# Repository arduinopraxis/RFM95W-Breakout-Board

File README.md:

# RFM95W-Breakout-Board
RFM92/95W Breakout-Board

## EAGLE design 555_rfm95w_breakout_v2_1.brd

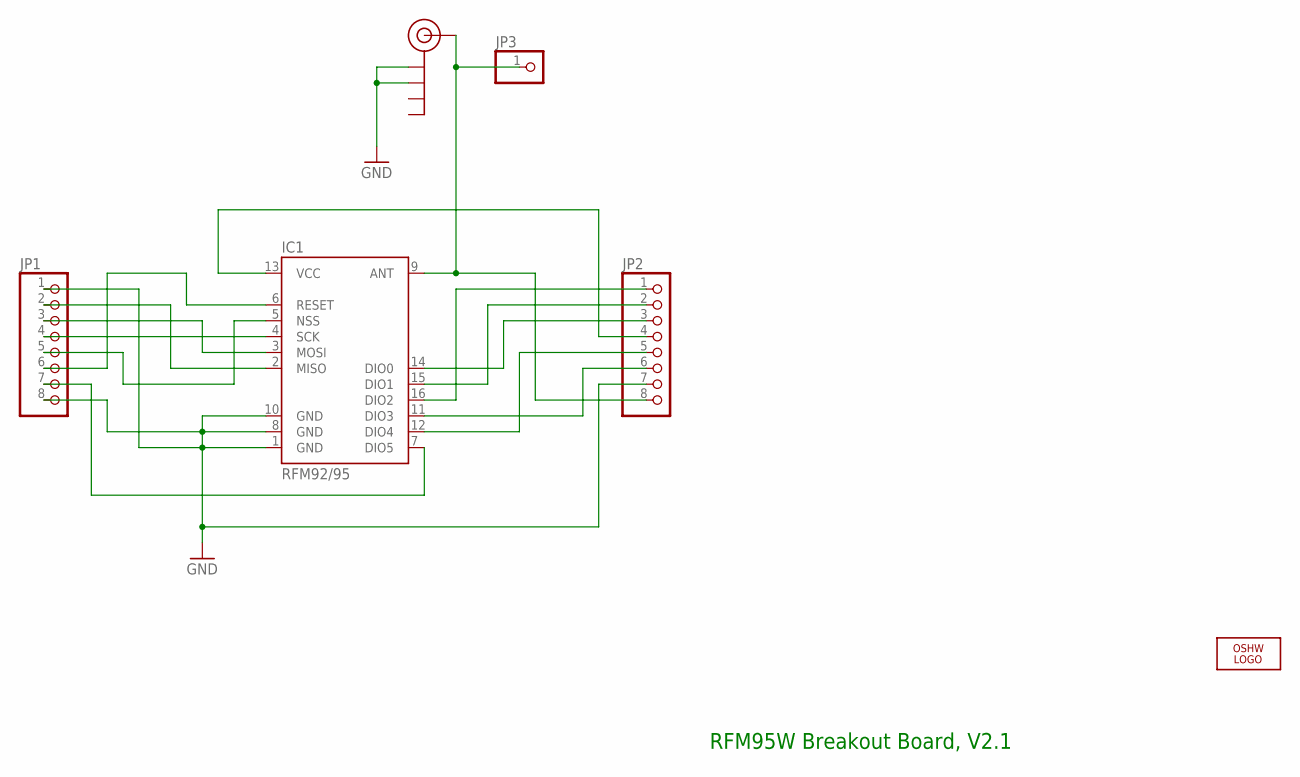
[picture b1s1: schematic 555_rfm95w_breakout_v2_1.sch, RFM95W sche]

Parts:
IC1: RFM92/95; RFM95W_SMD
J$1: ANT; SMA_EDGE
JP1, JP2: PINHD-1X8; 1X08
JP3: PINHD-1X1; 1X01
LOGO1: OSHW_LOGO_FILLX0100-NT; OSHW_FILLX100_NOTEXT

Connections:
GND: IC1.1 (GND), IC1.8 (GND), IC1.10 (GND), J$1.GND@0 (GND), J$1.GND@1 (GND), JP1.1, JP1.8, JP2.7
unnamed: IC1.9 (ANT), J$1.SIG (SIGNAL), JP2.8, JP3.1
unnamed: IC1.13 (VCC), JP2.4
unnamed: IC1.2 (MISO), JP1.2
unnamed: IC1.3 (MOSI), JP1.3
unnamed: IC1.4 (SCK), JP1.4
unnamed: IC1.5 (NSS), JP1.5
unnamed: IC1.6 (RESET), JP1.6
unnamed: IC1.7 (DIO5), JP1.7
unnamed: IC1.11 (DIO3), JP2.6
unnamed: IC1.12 (DIO4), JP2.5
unnamed: IC1.14 (DIO0), JP2.3
unnamed: IC1.15 (DIO1), JP2.2
unnamed: IC1.16 (DIO2), JP2.1

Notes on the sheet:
RFM95W Breakout Board, V2.1

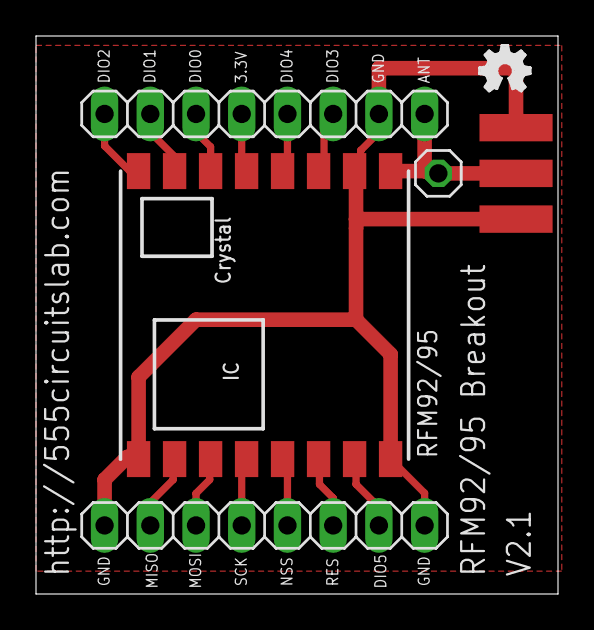
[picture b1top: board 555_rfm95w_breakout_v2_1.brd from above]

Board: 2 copper layers, 29.0 x 31.0 mm, 6 parts (0 on the bottom side), 14 nets.
